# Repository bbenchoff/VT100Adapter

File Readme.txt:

VT100 to ATX power supply adapter

This project adapts an off-the-shelf computer power supply to replace the power supply found in a Digital VT100 serial terminal.

As of now, this will not work with a VT103, as it does not generate BPOK and BDCOK signals. It should, however, work with the VT101 and VT102.

The terminal is not mounted to the PCB, allowing for positioning in various locations in the power supply bay of the VT100.

Included in this repo are Eagle schematic and board files, Gerbers in OSHPark format, and a BOM with Mouser listings of every component.

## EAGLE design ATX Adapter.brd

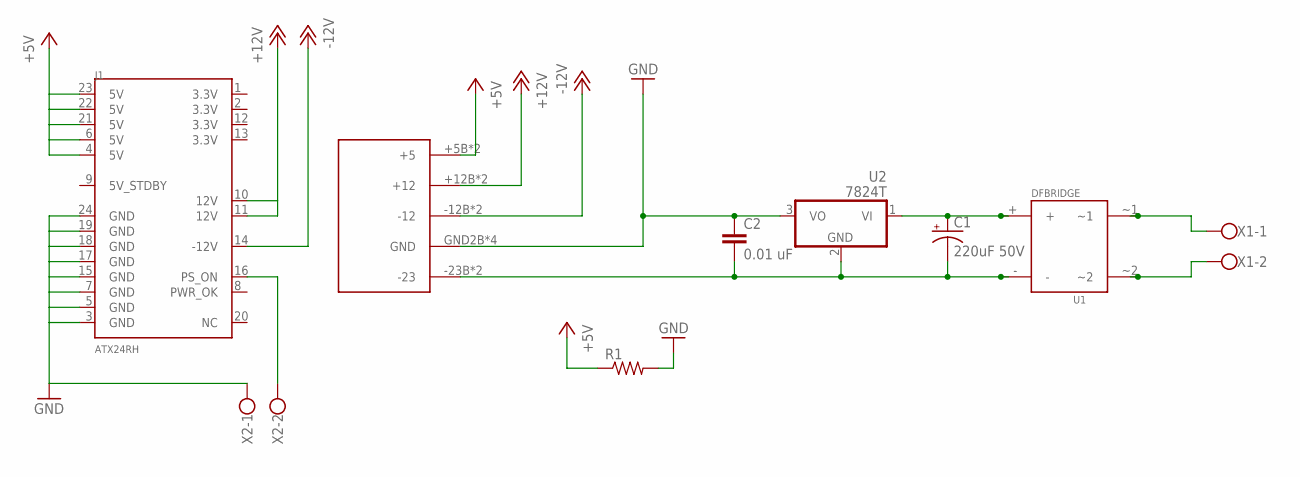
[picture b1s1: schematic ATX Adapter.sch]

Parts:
C1: 220uF 50V; CPOL-RADIAL-100UF-25V
C2: 0.01 uF; CAP-PTH-SMALLEZ
J1: ATX24RH; ATX24_RIGHT_ANGLE
R1: RESISTORPTH-2W; AXIAL-0.8
U1: DFBRIDGE
U2: 7824T; TO220H
U$1: VT100POWER
X1, X2: W237-102

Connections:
+5V: J1.4 (5V), J1.6 (5V), J1.21 (5V), J1.22 (5V), J1.23 (5V), R1.P$1 (1), U$1.+5B (+5), U$1.+5T (+5)
+12V: J1.10 (12V), J1.11 (12V), U$1.+12B (+12), U$1.+12T (+12)
-12V: J1.14 (-12V), U$1.-12B (-12), U$1.-12T (-12)
GND: C2.1, J1.3 (GND), J1.5 (GND), J1.7 (GND), J1.15 (GND), J1.17 (GND), J1.18 (GND), J1.19 (GND), J1.24 (GND), R1.P$2 (2), U2.3 (VO), U$1.GND2B (GND), U$1.GNDB1 (GND), U$1.GNDT1 (GND), U$1.GNDT2 (GND), X2.1
unnamed: U1.~1, X1.1
unnamed: U1.~2, X1.2
unnamed: C1.1 (+), U1.+, U2.1 (VI)
unnamed: C1.2 (-), C2.2, U1.-, U2.2 (GND), U$1.-23B (-23), U$1.-23T (-23)
unnamed: J1.16 (PS_ON), X2.2

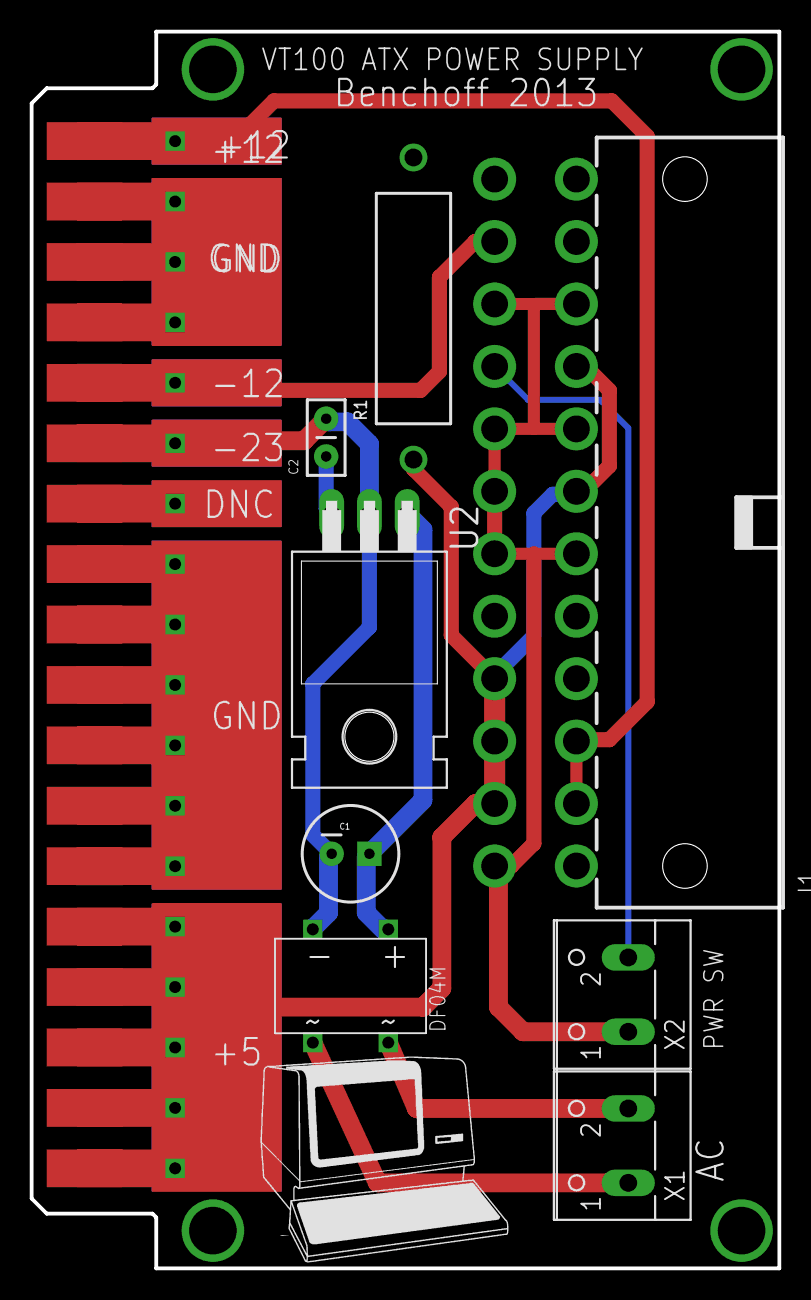
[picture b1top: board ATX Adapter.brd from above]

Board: 2 copper layers, 50.3 x 83.2 mm, 9 parts (0 on the bottom side), 9 nets.

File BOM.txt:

Part Value      Device      	Package               Description           			P/N

                                                                                                             
C1   220uF 50V  CAP_POLPTH1 	CPOL-RADIAL-100UF-25V Capacitor Polarized                                                                                                                                                                                                   
C2   0.01 uF    CAPEZ       	CAP-PTH-SMALLEZ       Capacitor                                                                                                                                                                                                             
J1   ATX24RH    ATX24RH     	ATX24_RIGHT_ANGLE     ATX24 Pin PRT-09498    			Mouser 538-39-30-0240

R1   6.8 Ohm	Resistor			      Wire-wound Resistor			Mouser 756-WHS5-6R8JT075
                                                      
U1   DFBRIDGE   Diode Bridge			                                               	Mouser 625-DF04MA-E3                                                                                                                                                                                    
U2   7824T      7824T       	TO220H                Positive Voltage Regulator	       	Mouser 755-BA17824T                                                                                                                                                                      
X1   X1           	    		              Terminal Block                            Mouser 571-282856-2                                                                                                                                                 
X2   X2           	    		              Terminal Block                            Mouser 571-282856-2

T1		Transformer			      Power Transformers 115/230 6VA 24VCT	Mouser 546-186B24

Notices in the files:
parts and their libraries:
SparkFun-Connectors: Licensing: CC v3.0 Share-Alike You are welcome to use this library for commercial purposes.
